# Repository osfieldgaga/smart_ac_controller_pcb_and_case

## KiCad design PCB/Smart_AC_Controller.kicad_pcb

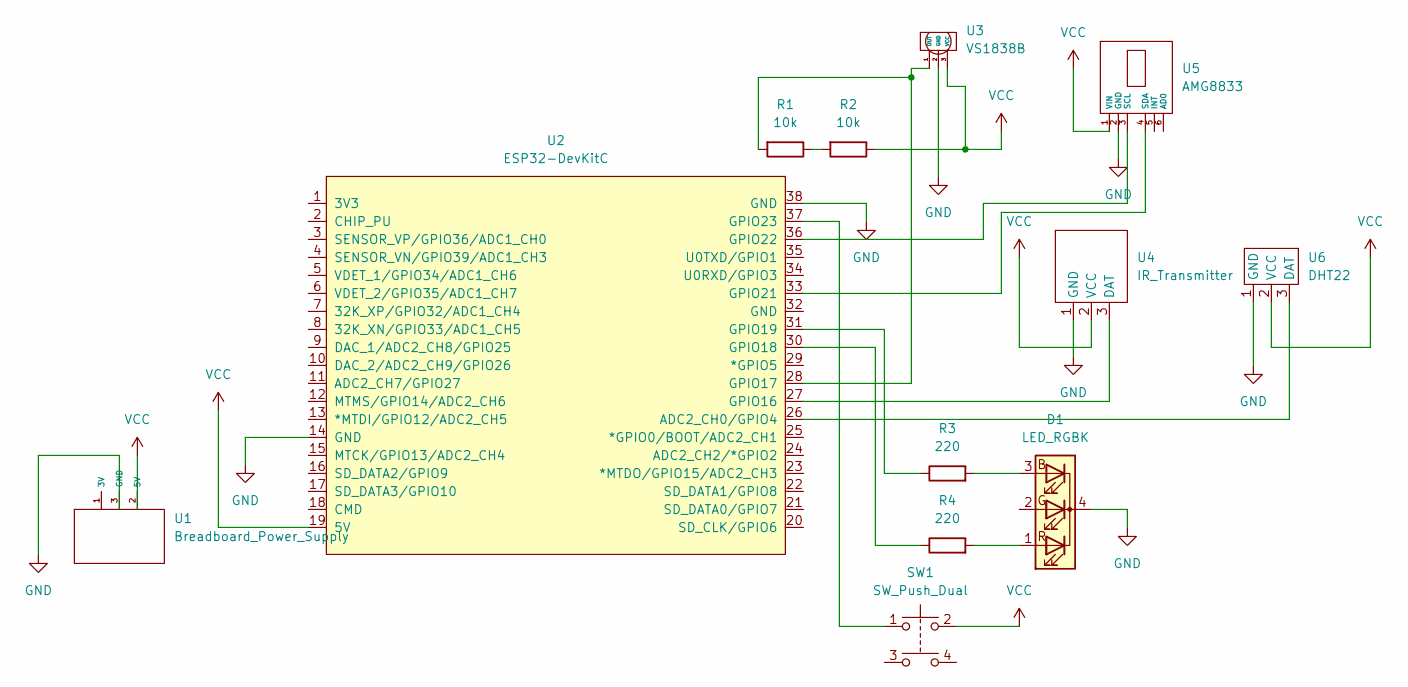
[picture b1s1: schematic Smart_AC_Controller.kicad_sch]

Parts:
D1: LED_RGBK; LED_D5.0mm-4_RGB
R1, R2: 10k; R_Axial_DIN0207_L6.3mm_D2.5mm_P7.62mm_Horizontal
R3, R4: 220; R_Axial_DIN0207_L6.3mm_D2.5mm_P7.62mm_Horizontal
SW1: SW_Push_Dual; SW_PUSH-12mm
U1: Breadboard_Power_Supply; Breadboard Power Supply
U2: ESP32-DevKitC
U3: VS1838B
U4: IR_Transmitter
U5: AMG8833
U6: DHT22

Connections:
GND: D1.4 (K), U1.3 (GND), U2.14 (GND), U2.38 (GND), U3.2 (GND), U4.1 (GND), U5.2 (GND), U6.1 (GND)
unnamed: D1.1 (RA), R4.2
unnamed: D1.3 (BA), R3.2
unnamed: R1.1, R2.2
unnamed: R1.2, U2.28 (GPIO17), U3.1 (OUT)
unnamed: R3.1, U2.31 (GPIO19)
unnamed: R4.1, U2.30 (GPIO18)
unnamed: SW1.1, U2.37 (GPIO23)
unnamed: U2.26 (ADC2_CH0/GPIO4), U6.3 (DAT)
unnamed: U2.27 (GPIO16), U4.3 (DAT)
unnamed: U2.33 (GPIO21), U5.4 (SDA)
unnamed: U2.36 (GPIO22), U5.3 (SCL)
VCC: R2.1, SW1.2, U1.2 (5V), U2.19 (5V), U3.3 (VCC), U4.2 (VCC), U5.1 (VIN), U6.2 (VCC)

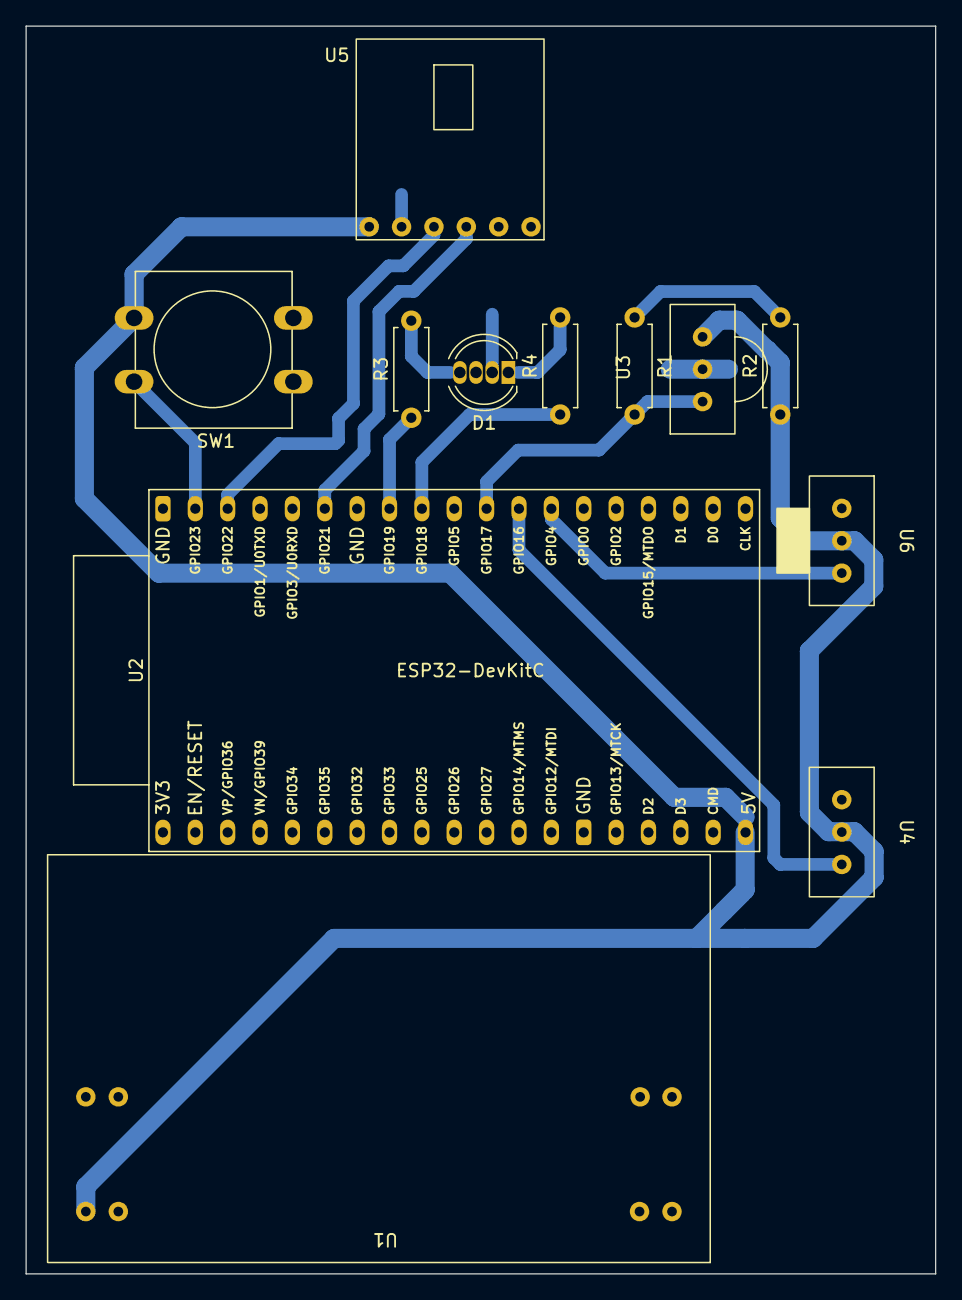
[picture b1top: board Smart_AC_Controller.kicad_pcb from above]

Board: 2 copper layers, 71.4 x 97.9 mm, 12 parts (0 on the bottom side), 13 nets.

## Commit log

2022-10-05 init commit
